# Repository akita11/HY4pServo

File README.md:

# HY4pServo

M5Stack等のHY4pコネクタ（いわゆるGrove互換コネクタ）にサーボモータをつなぐための変換ボード。
M5Stackシリーズは電源系統が弱く、そのままだとサーボ動作時にリセットがかかる場合が多いので、電源ラインに100uFのバイパスコンデンサをいれてあります。

# How to use

M5Stack等のHY4pコネクタにGroveケーブルで接続し、反対側にサーボモータ（端子の並びがV-G-Sのもの）をつなぎます。
UIFlowのServoユニットやArduinoIDEのServoライブラリ等で使用します。

※サーボモータの信号線は、HY4pコネクタのVDD線の隣の信号線に接続されています。

※コネクタの電源がそのままサーボの電源につながっています。5Vが必要なサーボは、5V電源電圧使用してください。

# Author

Junichi Akita (akita@ifdl.jp, @akita11)

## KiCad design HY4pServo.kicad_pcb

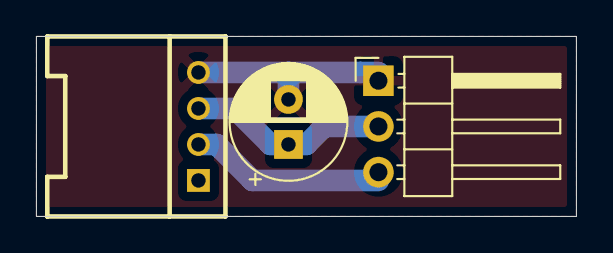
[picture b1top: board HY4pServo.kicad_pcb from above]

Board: 2 copper layers, 30.0 x 10.0 mm, 3 parts (0 on the bottom side), 3 nets.

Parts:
C1: 100u; CP_Radial_D6.3mm_P2.50mm
CN1: CON_GROVE; CON_GROVE_H
J1: Conn_01x03; PinHeader_1x03_P2.54mm_Horizontal

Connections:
GND: C1.2, CN1.4, J1.1
unnamed: C1.1, CN1.3, J1.2
unnamed: CN1.2, J1.3

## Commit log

2021-02-04 電源電圧について追記
